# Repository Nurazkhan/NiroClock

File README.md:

# NiroClock
Amazing clock that looks like dumb terminal, but actually very smart.

I made this clock with the help of hackClub. You can find useful references/examples in [BlareV2]([url](https://stardance.hackclub.com/missions/blare)) section.

## Features
* 76x284px for different modes of time display.
* 5 Cherry MX style Keys for best experience.
* 3D printed perfect case that looks like old computer giving +++Aura
* .ino firmware containing 5 pages and each page with button control.
* the noisy buzzer that won't let you sleep after alarm.

## CAD Model
CAD consists of a total of 4 parts: Main bottom, main cover, back plate, front plate.
The case and the cover for it fit together with 4*M3 screws and heatset inserts.
The back plate is also attached using 2*M3 and well as front plate.
The case has space for keys and display, so it fits perfectly.

Made in OnShape. by Nurazkhan (me).

## PCB

Schematic was made in KiCad.

PCB routing was also made in KiCad Software. Footprints for keys were imported from recommended resources; you can also find [it]([url](https://github.com/sszczep/kicad-libraries)).

## Firmware Overview
The NiroPad Works on c++ used in arduino IDE
Main functions are:
* 5 keys for clock control.
* buzzer to wake you up.
* 5 different pages qith unique control.
* change display mode from HH:MM:SS or HH:MM.
* Start Secondmeter

## BOM
* Cherry MX style switches	5
* Seeed XIAO ESP32C3	1
* Blank DSA caps	5
* 2.25in TFT Screen	1
* Custom PCB	1
* 3.3V Piezo Buzzer	
* 3d printed enclosure	4
* 2.54mm 8 Pin Male Header	1
* M3x16mm 	4
* M3x8mm 	4
* M3x5x4 Heatset Inserts	8
* 20cm Female-Female Jumper Wires	8

The process of designing and creation you can see in the [website]([url]https://stardance.hackclub.com/projects/63343)

Thank you!
#hackClub

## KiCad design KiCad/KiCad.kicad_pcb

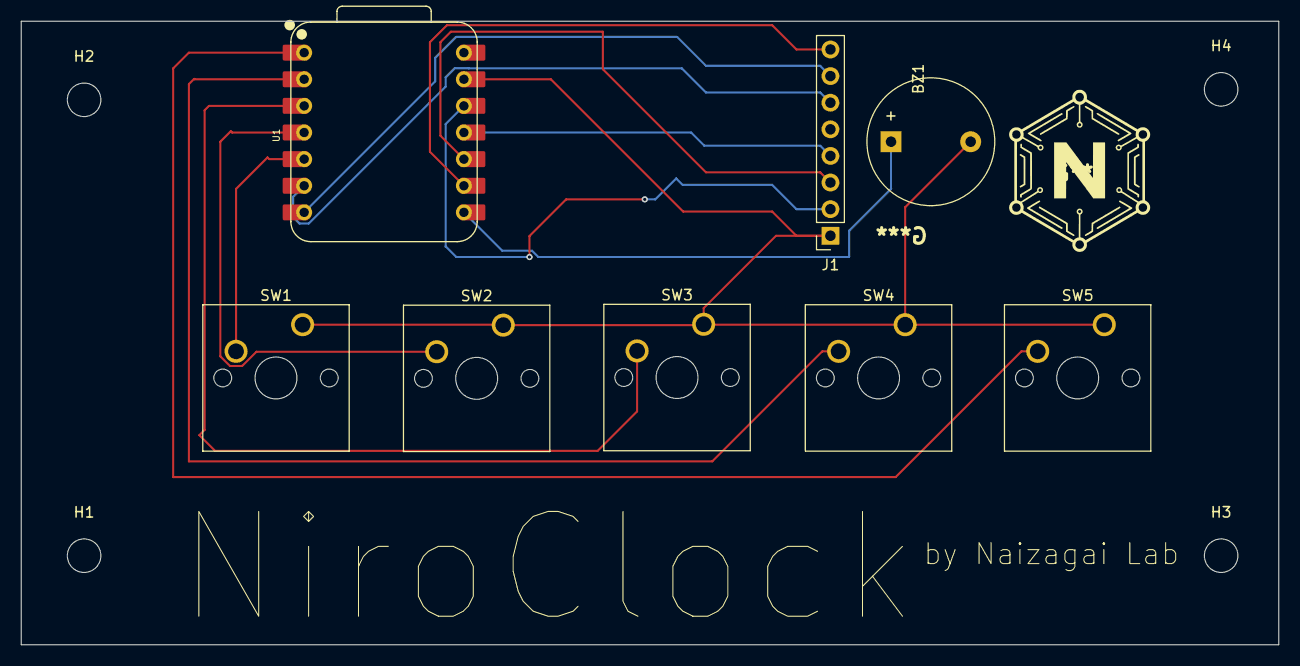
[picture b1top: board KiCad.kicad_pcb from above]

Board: 2 copper layers, 120.0 x 59.5 mm, 12 parts (0 on the bottom side), 13 nets.

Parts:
BZ1: Buzzer; Buzzer_12x9.5RM7.6
H1, H2, H3, H4: MountingHole; MountingHole_3.2mm_M3
J1: Conn_01x08_Pin; PinSocket_1x08_P2.54mm_Vertical
SW1, SW3, SW4, SW5: SW_Push; SW_Cherry_MX_1.00u_PCB
SW2: SW_Push; SW_Cherry_MX_1.25u_PCB
U1: XIAO-ESP32-C3-SMD; XIAO-ESP32-C3-DIP

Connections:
+3V3: J1.2, U1.12 (3V3_OUT)
/BL: J1.8, U1.9 (D8)
/CS: J1.7, U1.7 (D6)
/DC: J1.6, U1.6 (D5)
/SCL: J1.3, U1.10 (D9/BOOT)
/SDA: J1.4, U1.11 (D10)
GND: BZ1.2 (-), J1.1, SW1.1, SW2.1, SW3.1, SW4.1, SW5.1, U1.13 (GND)
unnamed: BZ1.1 (+), U1.8 (D7)
unnamed: SW5.2, U1.1 (D0)
unnamed: SW4.2, U1.2 (D1)
unnamed: SW3.2, U1.3 (D2)
unnamed: SW2.2, U1.4 (D3)
unnamed: SW1.2, U1.5 (D4)
